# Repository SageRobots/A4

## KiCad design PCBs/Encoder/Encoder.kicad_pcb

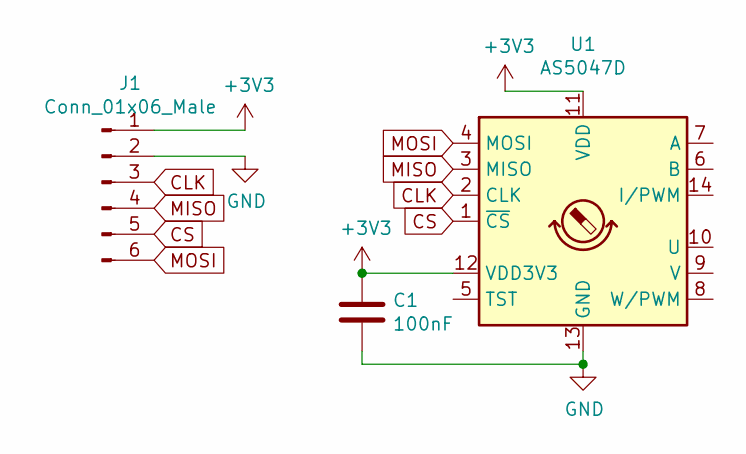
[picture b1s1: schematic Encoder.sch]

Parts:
C1: 100nF; C_0805_2012Metric_Pad1.18x1.45mm_HandSolder
J1: Conn_01x06_Male; PinHeader_2x03_P2.00mm_Vertical
U1: AS5047D; TSSOP-14_4.4x5mm_P0.65mm

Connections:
+3V3: C1.1, J1.1, U1.11 (VDD), U1.12 (VDD3V3)
CLK: J1.3, U1.2 (CLK)
CS: J1.5, U1.1 (~CS)
GND: C1.2, J1.2, U1.13 (GND)
MISO: J1.4, U1.3 (MISO)
MOSI: J1.6, U1.4 (MOSI)

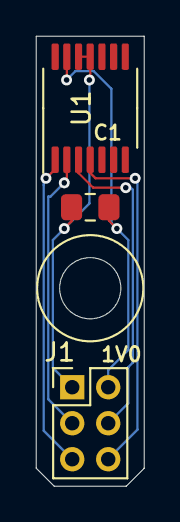
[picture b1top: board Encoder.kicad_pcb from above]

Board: 2 copper layers, 6.0 x 25.0 mm, 3 parts (0 on the bottom side), 6 nets.

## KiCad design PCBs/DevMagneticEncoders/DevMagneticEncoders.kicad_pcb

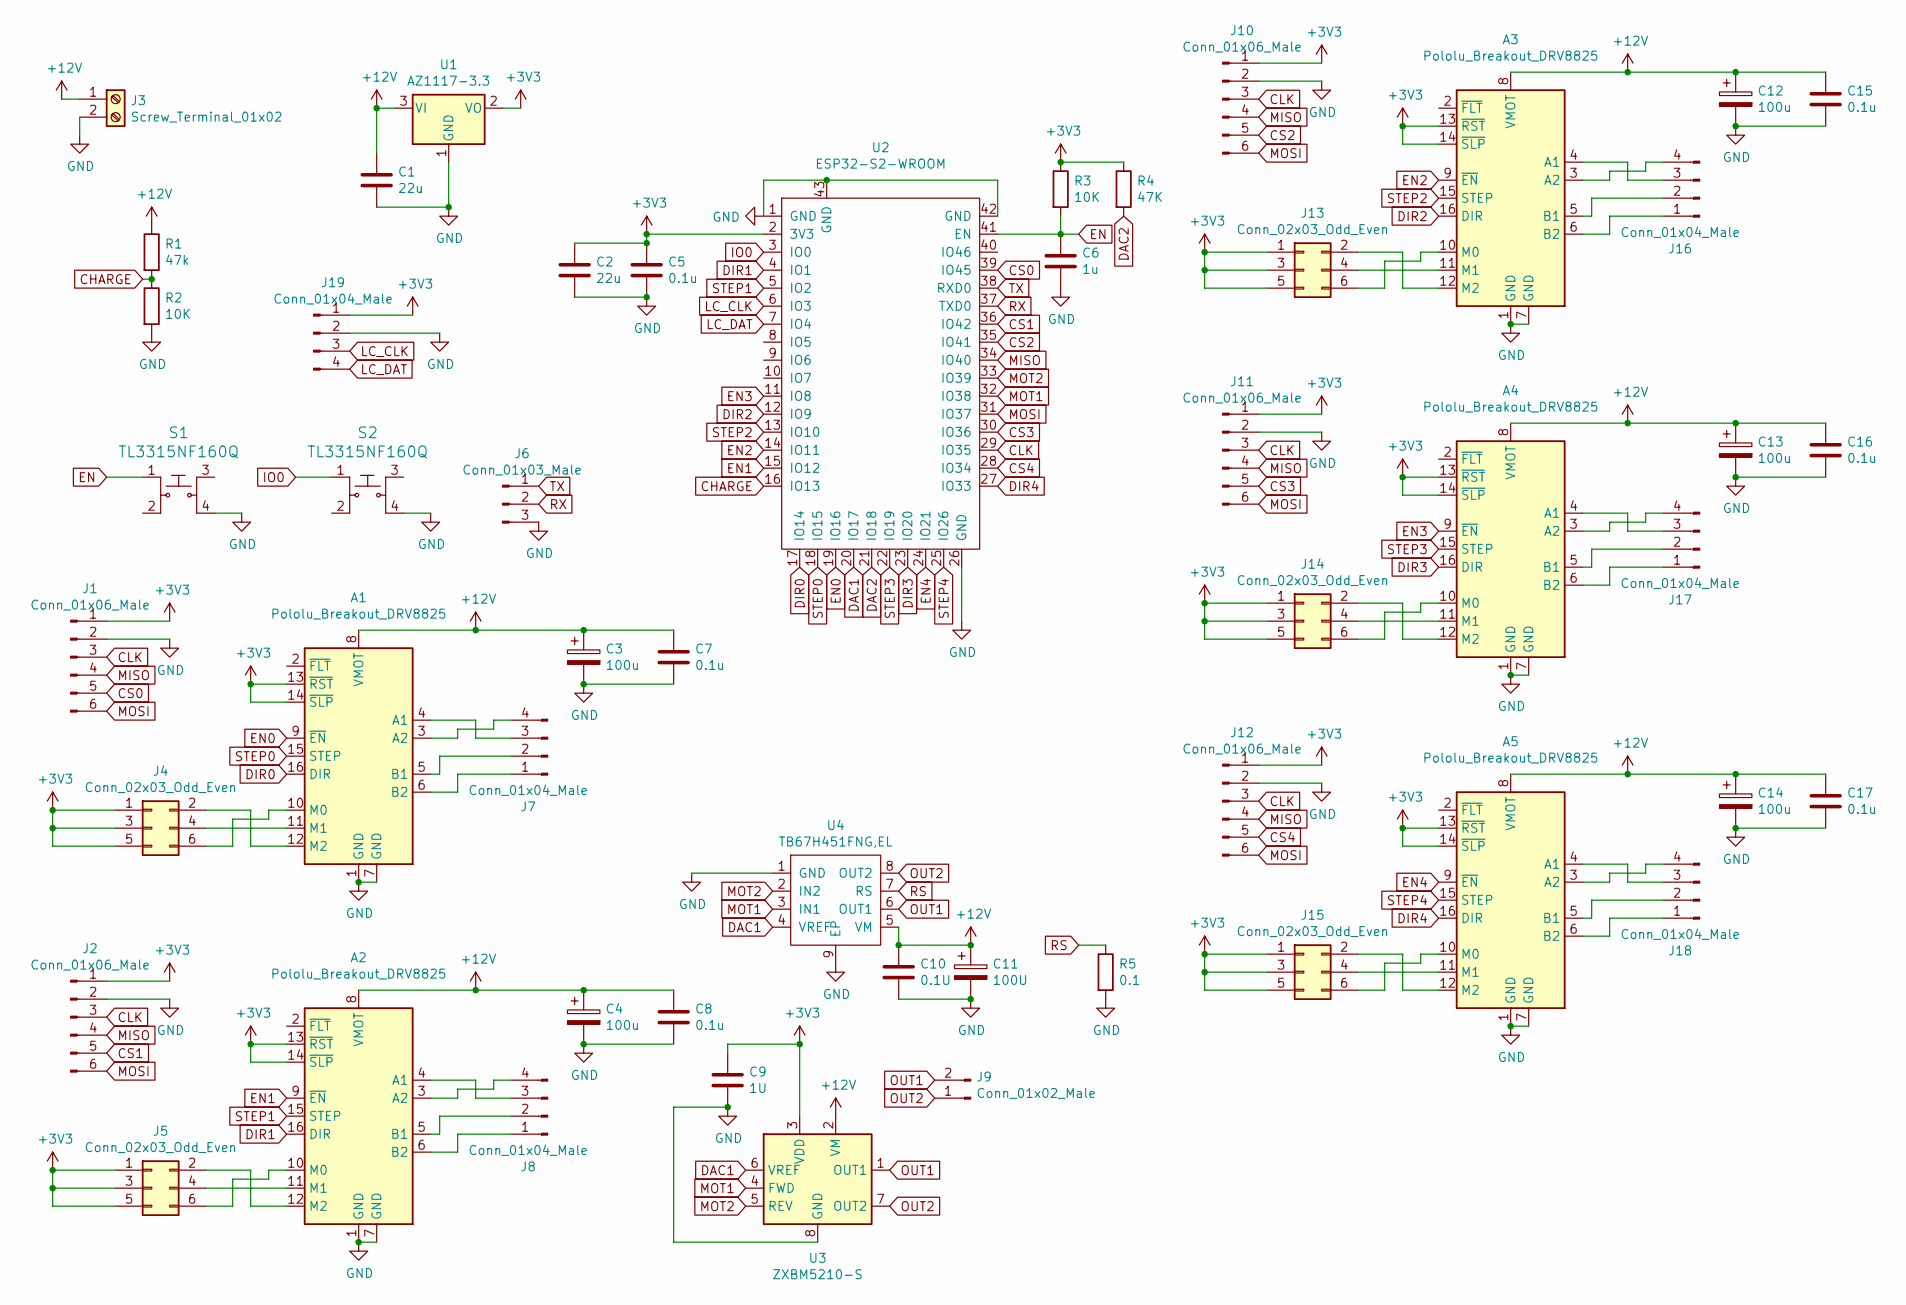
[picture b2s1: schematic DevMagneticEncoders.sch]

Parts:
A1, A2, A3, A4, A5: Pololu_Breakout_DRV8825; Pololu_Breakout-16_15.2x20.3mm
C1, C2: 22u; C_0805_2012Metric_Pad1.18x1.45mm_HandSolder
C3, C4, C12, C13, C14: 100u; CP_Elec_6.3x7.7
C5, C7, C8, C15, C16, C17: 0.1u; C_0805_2012Metric_Pad1.18x1.45mm_HandSolder
C6: 1u; C_0805_2012Metric_Pad1.18x1.45mm_HandSolder
C9: 1U; C_0805_2012Metric_Pad1.18x1.45mm_HandSolder
C10: 0.1U; C_0805_2012Metric_Pad1.18x1.45mm_HandSolder
C11: 100U; CP_Elec_6.3x7.7
J1, J2, J10, J11, J12: Conn_01x06_Male; JST_XH_B6B-XH-A_1x06_P2.50mm_Vertical
J3: Screw_Terminal_01x02; TerminalBlock_Phoenix_MKDS-1,5-2_1x02_P5.00mm_Horizontal
J4, J5, J13, J14, J15: Conn_02x03_Odd_Even; PinHeader_2x03_P2.54mm_Vertical
J6: Conn_01x03_Male; PinHeader_1x03_P2.54mm_Vertical
J7, J8, J16, J17, J18, J19: Conn_01x04_Male; JST_XH_B4B-XH-A_1x04_P2.50mm_Vertical
J9: Conn_01x02_Male; JST_XH_B2B-XH-A_1x02_P2.50mm_Vertical
R1: 47k; R_0805_2012Metric_Pad1.20x1.40mm_HandSolder
R2, R3: 10K; R_0805_2012Metric_Pad1.20x1.40mm_HandSolder
R4: 47K; R_0805_2012Metric_Pad1.20x1.40mm_HandSolder
R5: 0.1; R_0805_2012Metric_Pad1.20x1.40mm_HandSolder
S1, S2: TL3315NF160Q; TL3305AF160QG; MPN TL3315NF160Q; Digi-Key_PN EG4621CT-ND
U1: AZ1117-3.3; SOT-223-3_TabPin2
U2: ESP32-S2-WROOM
U3: ZXBM5210-S; SOIC-8_3.9x4.9mm_P1.27mm
U4: TB67H451FNG,EL; SOIC-8-1EP_3.9x4.9mm_P1.27mm_EP2.29x3mm_ThermalVias

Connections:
+3V3: A1.13 (~RST), A1.14 (~SLP), A2.13 (~RST), A2.14 (~SLP), A3.13 (~RST), A3.14 (~SLP), A4.13 (~RST), A4.14 (~SLP), A5.13 (~RST), A5.14 (~SLP), C2.1, C5.1, C9.1, J1.1, J2.1, J4.1, J4.3, J4.5, J5.1, J5.3, J5.5, J10.1, J11.1, J12.1, J13.1, J13.3, J13.5, J14.1, J14.3, J14.5, J15.1, J15.3, J15.5, J19.1, R3.1, R4.1, U1.2 (VO), U2.2 (3V3), U3.3 (VDD)
+12V: A1.8 (VMOT), A2.8 (VMOT), A3.8 (VMOT), A4.8 (VMOT), A5.8 (VMOT), C1.1, C3.1, C4.1, C7.1, C8.1, C10.1, C11.1, C12.1, C13.1, C14.1, C15.1, C16.1, C17.1, J3.1, R1.1, U1.3 (VI), U3.2 (VM), U4.5 (VM)
CHARGE: R1.2, R2.1, U2.16 (IO13)
CLK: J1.3, J2.3, J10.3, J11.3, J12.3, U2.29 (IO35)
CS0: J1.5, U2.39 (IO45)
CS1: J2.5, U2.36 (IO42)
CS2: J10.5, U2.35 (IO41)
CS3: J11.5, U2.30 (IO36)
CS4: J12.5, U2.28 (IO34)
DAC1: U2.20 (IO17), U3.6 (VREF), U4.4 (VREF)
DAC2: R4.2, U2.21 (IO18)
DIR0: A1.16 (DIR), U2.17 (IO14)
DIR1: A2.16 (DIR), U2.4 (IO1)
DIR2: A3.16 (DIR), U2.12 (IO9)
DIR3: A4.16 (DIR), U2.23 (IO20)
DIR4: A5.16 (DIR), U2.27 (IO33)
EN: C6.1, R3.2, S1.1, U2.41 (EN)
EN0: A1.9 (~EN), U2.19 (IO16)
EN1: A2.9 (~EN), U2.15 (IO12)
EN2: A3.9 (~EN), U2.14 (IO11)
EN3: A4.9 (~EN), U2.11 (IO8)
EN4: A5.9 (~EN), U2.24 (IO21)
GND: A1.1 (GND), A1.7 (GND), A2.1 (GND), A2.7 (GND), A3.1 (GND), A3.7 (GND), A4.1 (GND), A4.7 (GND), A5.1 (GND), A5.7 (GND), C1.2, C2.2, C3.2, C4.2, C5.2, C6.2, C7.2, C8.2, C9.2, C10.2, C11.2, C12.2, C13.2, C14.2, C15.2, C16.2, C17.2, J1.2, J2.2, J3.2, J6.3, J10.2, J11.2, J12.2, J19.2, R2.2, R5.2, S1.4, S2.4, U1.1 (GND), U2.1 (GND), U2.26 (GND), U2.42 (GND), U2.43 (GND), U3.8 (GND), U4.1 (GND), U4.9 (EP)
IO0: S2.1, U2.3 (IO0)
LC_CLK: J19.3, U2.6 (IO3)
LC_DAT: J19.4, U2.7 (IO4)
MISO: J1.4, J2.4, J10.4, J11.4, J12.4, U2.34 (IO40)
MOSI: J1.6, J2.6, J10.6, J11.6, J12.6, U2.31 (IO37)
MOT1: U2.32 (IO38), U3.4 (FWD), U4.3 (IN1)
MOT2: U2.33 (IO39), U3.5 (REV), U4.2 (IN2)
unnamed: A1.3 (A2), J7.4
unnamed: A1.4 (A1), J7.3
unnamed: A1.5 (B1), J7.2
unnamed: A1.6 (B2), J7.1
unnamed: A1.10 (M0), J4.6
unnamed: A1.11 (M1), J4.4
unnamed: A1.12 (M2), J4.2
unnamed: A2.3 (A2), J8.4
unnamed: A2.4 (A1), J8.3
unnamed: A2.5 (B1), J8.2
unnamed: A2.6 (B2), J8.1
unnamed: A2.10 (M0), J5.6
unnamed: A2.11 (M1), J5.4
unnamed: A2.12 (M2), J5.2
unnamed: A3.3 (A2), J16.4
unnamed: A3.4 (A1), J16.3
unnamed: A3.5 (B1), J16.2
unnamed: A3.6 (B2), J16.1
unnamed: A3.10 (M0), J13.6
unnamed: A3.11 (M1), J13.4
unnamed: A3.12 (M2), J13.2
unnamed: A4.3 (A2), J17.4
unnamed: A4.4 (A1), J17.3
unnamed: A4.5 (B1), J17.2
unnamed: A4.6 (B2), J17.1
unnamed: A4.10 (M0), J14.6
unnamed: A4.11 (M1), J14.4
unnamed: A4.12 (M2), J14.2
unnamed: A5.3 (A2), J18.4
unnamed: A5.4 (A1), J18.3
unnamed: A5.5 (B1), J18.2
unnamed: A5.6 (B2), J18.1
unnamed: A5.10 (M0), J15.6
unnamed: A5.11 (M1), J15.4
unnamed: A5.12 (M2), J15.2
OUT1: J9.2, U3.1 (OUT1), U4.6 (OUT1)
OUT2: J9.1, U3.7 (OUT2), U4.8 (OUT2)
RS: R5.1, U4.7 (RS)
RX: J6.2, U2.37 (TXD0)
STEP0: A1.15 (STEP), U2.18 (IO15)
STEP1: A2.15 (STEP), U2.5 (IO2)
STEP2: A3.15 (STEP), U2.13 (IO10)
STEP3: A4.15 (STEP), U2.22 (IO19)
STEP4: A5.15 (STEP), U2.25 (IO26)
TX: J6.1, U2.38 (RXD0)

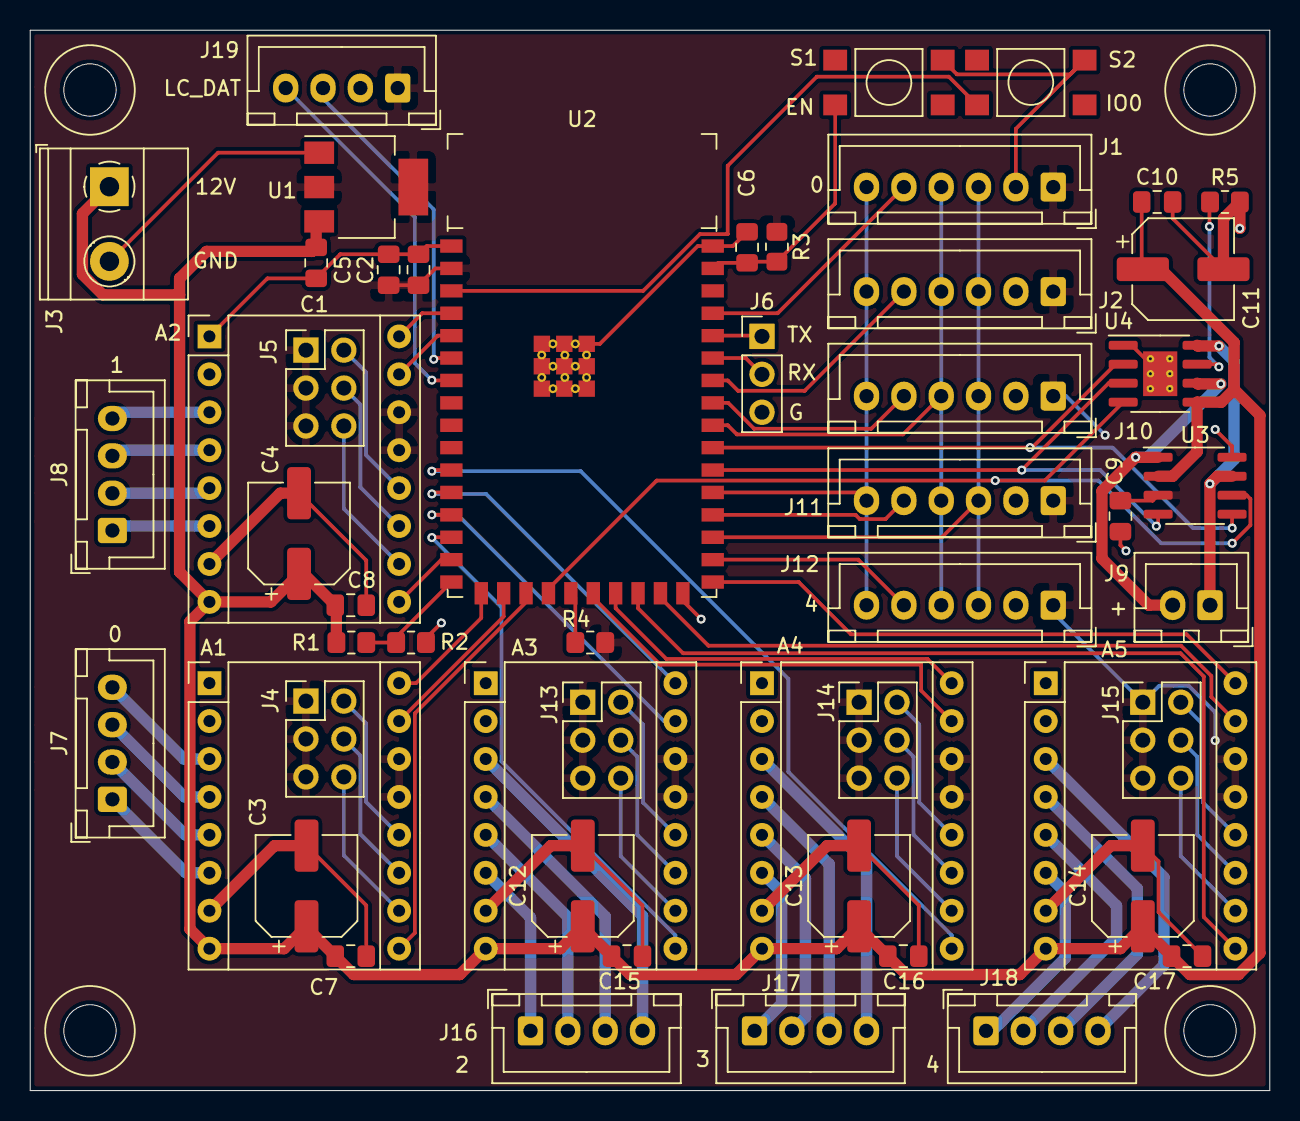
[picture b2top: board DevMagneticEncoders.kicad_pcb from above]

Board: 2 copper layers, 83.0 x 71.0 mm, 52 parts (0 on the bottom side), 75 nets.

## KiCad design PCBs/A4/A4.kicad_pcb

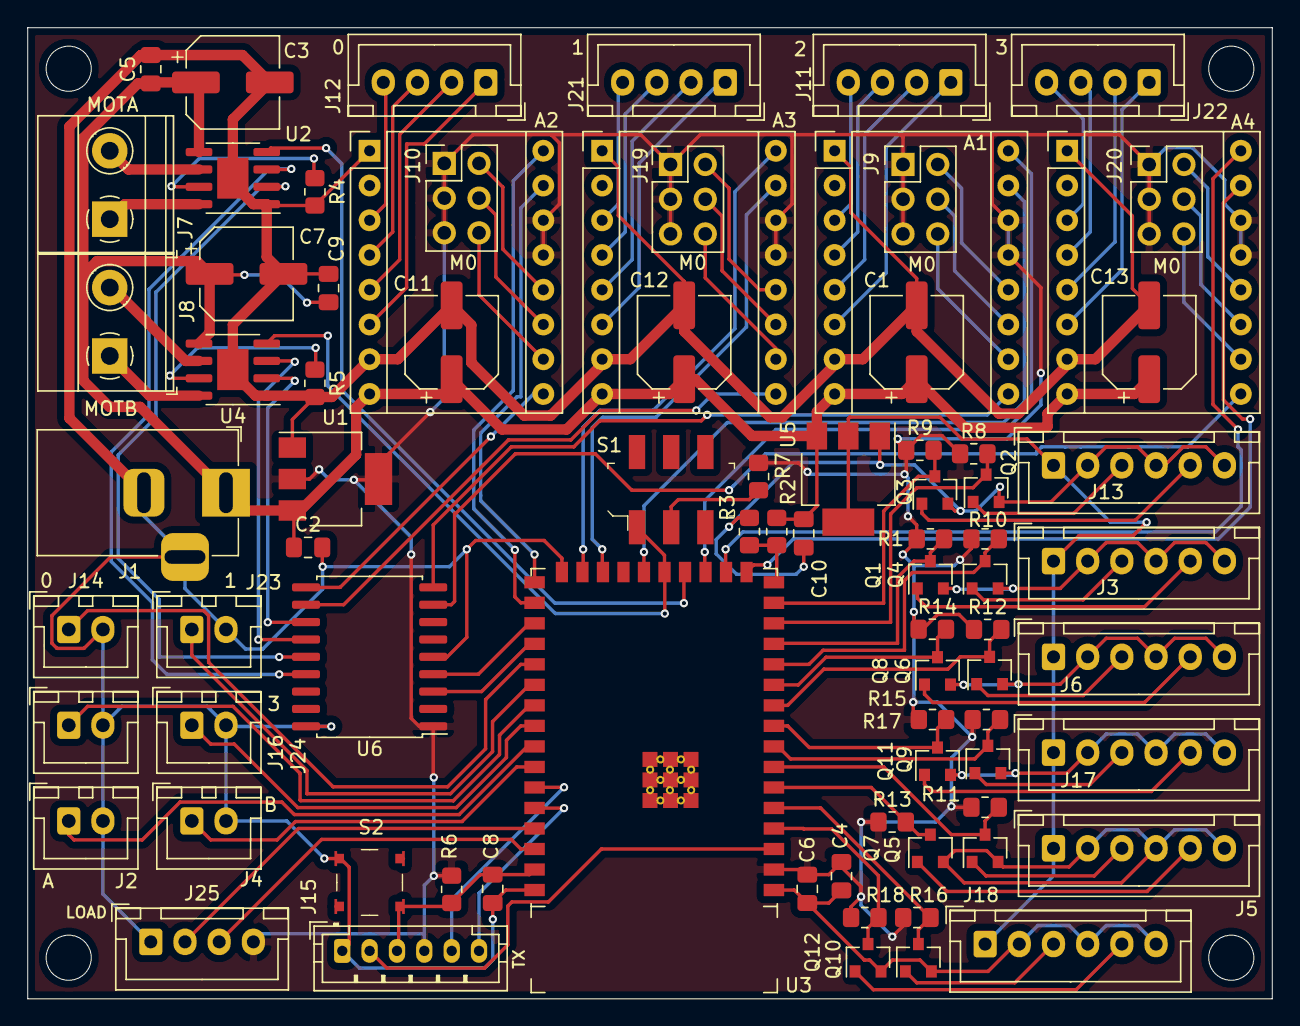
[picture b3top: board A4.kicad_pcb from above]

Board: 2 copper layers, 91.0 x 71.0 mm, 80 parts (0 on the bottom side), 96 nets.

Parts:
A1, A2, A3, A4: Pololu_Breakout_DRV8825; Pololu_Breakout-16_15.2x20.3mm
C1, C3, C7, C11, C12, C13: 100u; CP_Elec_6.3x7.7
C2, C4, C10: 22u; C_0805_2012Metric_Pad1.18x1.45mm_HandSolder
C5, C6, C9: 0.1u; C_0805_2012Metric_Pad1.18x1.45mm_HandSolder
C8: 1u; C_0805_2012Metric_Pad1.18x1.45mm_HandSolder
J1: Barrel_Jack_Switch; BarrelJack_Horizontal
J2, J4, J14, J16, J23, J24: Conn_01x02_Male; JST_XH_B2B-XH-A_1x02_P2.50mm_Vertical
J3, J5, J6, J13, J17, J18: Conn_01x06_Male; JST_XH_B6B-XH-A_1x06_P2.50mm_Vertical
J7, J8: Screw_Terminal_01x02; TerminalBlock_Phoenix_MKDS-1,5-2_1x02_P5.00mm_Horizontal
J9, J10, J19, J20: Conn_02x03_Odd_Even; PinHeader_2x03_P2.54mm_Vertical
J11, J12, J21, J22, J25: Conn_01x04_Male; JST_XH_B4B-XH-A_1x04_P2.50mm_Vertical
J15: Conn_01x06_Male; JST_PH_B6B-PH-K_1x06_P2.00mm_Vertical
Q1, Q2, Q3, Q4, Q5, Q6, Q7, Q8, Q9, Q10, Q11, Q12: 2N7002; SOT-23
R1, R3, R6, R8, R9, R10, R11, R12, R13, R14, R15, R16, R17, R18: 10K; R_0805_2012Metric_Pad1.20x1.40mm_HandSolder
R2: 47k; R_0805_2012Metric_Pad1.20x1.40mm_HandSolder
R4, R5: 0.1; R_0805_2012Metric_Pad1.20x1.40mm_HandSolder
R7: 47K; R_0805_2012Metric_Pad1.20x1.40mm_HandSolder
S1: JS202011SCQN; Switch_Slide_JS202011SCQN
S2: TL3315NF160Q; Switch_Tactile_SMD_4.5x4.5mm_TL3315NF160Q
U1: AZ1117-3.3; SOT-223-3_TabPin2
U2, U4: TB67H451FNG,EL; SOIC-8-1EP_3.9x4.9mm_P1.27mm_EP2.29x3mm
U3: ESP32-S2-WROOM
U5: AZ1117-5.0; SOT-223-3_TabPin2
U6: MCP23009; SOIC-18W_7.5x11.6mm_P1.27mm

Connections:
+3V3: A1.13, A1.14, A2.13, A2.14, A3.13, A3.14, A4.13, A4.14, C4.1, C6.1, J9.1, J9.3, J9.5, J10.1, J10.3, J10.5, J15.4, J19.1, J19.3, J19.5, J20.1, J20.3, J20.5, J25.4, R1.1, R6.1, R7.1, R8.1, R9.1, R10.1, R11.1, R12.1, R13.1, R14.1, R15.1, R16.1, R17.1, R18.1, U1.2, U3.2, U6.1
+5V: J3.1, J5.1, J6.1, J13.1, J17.1, J18.1, U5.2
+12V: A1.8, A2.8, A3.8, A4.8, C1.1, C2.1, C3.1, C5.1, C7.1, C9.1, C10.1, C11.1, C12.1, C13.1, J1.1, R2.1, U1.3, U2.5, U4.5, U5.3
CHARGE: R2.2, R3.1, U3.16
CLK: J25.3, U3.40
DAC1: U2.4, U3.20
DAC2: S1.1, U3.21, U4.4
DAT: J25.2, U3.39
DIR0: A2.16, U3.28
DIR1: A3.16, U3.25
DIR2: A1.16, U3.19
DIR3: A4.16, U3.18
EN: C8.1, J15.3, R6.2, S2.1, U3.41
EN0: A2.9, U6.10
EN1: A3.9, U6.11
EN2: A1.9, U6.9
EN3: A4.9, U6.8
ENC0A: Q6.3, R12.2, U3.10
ENC0A_5V: J6.3, Q6.1
ENC0B: Q8.3, R14.2, U3.11
ENC0B_5V: J6.5, Q8.1
ENC1A: Q9.3, R15.2, U3.8
ENC1A_5V: J17.3, Q9.1
ENC1B: Q11.3, R17.2, U3.9
ENC1B_5V: J17.5, Q11.1
ENC2A: Q5.3, R11.2, U3.7
ENC2A_5V: J5.3, Q5.1
ENC2B: Q7.3, R13.2, U3.6
ENC2B_5V: J5.5, Q7.1
ENC3A: Q10.3, R16.2, U3.5
ENC3A_5V: J18.3, Q10.1
ENC3B: Q12.3, R18.2, U3.4
ENC3B_5V: J18.5, Q12.1
ENCAA: Q2.3, R8.2, U3.14
ENCAA_5V: J13.3, Q2.1
ENCAB: Q3.3, R9.2, U3.15
ENCAB_5V: J13.5, Q3.1
ENCBA: Q4.3, R10.2, U3.12
ENCBA_5V: J3.3, Q4.1
ENCBB: Q1.3, R1.2, U3.13
ENCBB_5V: J3.5, Q1.1
GND: A1.1, A1.7, A2.1, A2.7, A3.1, A3.7, A4.1, A4.7, C1.2, C2.2, C3.2, C4.2, C5.2, C6.2, C7.2, C8.2, C9.2, C10.2, C11.2, C12.2, C13.2, J1.2, J1.3, J2.2, J3.2, J3.4, J3.6, J4.2, J5.2, J5.4, J5.6, J6.2, J6.4, J6.6, J13.2, J13.4, J13.6, J14.2, J15.1, J16.2, J17.2, J17.4, J17.6, J18.2, J18.4, J18.6, J23.2, J24.2, J25.1, Q1.2, Q2.2, Q3.2, Q4.2, Q5.2, Q6.2, Q7.2, Q8.2, Q9.2, Q10.2, Q11.2, Q12.2, R3.2, R4.2, R5.2, S2.4, U1.1, U2.1, U2.9, U3.1, U3.26, U3.42, U4.1, U4.9, U5.1, U6.5, U6.18
HOM0: J14.1, U3.31
HOM1: J23.1, U3.32
HOM2: J16.1, U3.33
HOM3: J24.1, U3.34
HOMA: J2.1, U3.35
HOMB: J4.1, U3.36
IO0: J15.2, U3.3
MOTA1: U2.3, U6.15
MOTA2: U2.2, U6.14
MOTB1: U4.3, U6.13
MOTB2: U4.2, U6.12
unnamed: A1.3, J11.4
unnamed: A1.4, J11.3
unnamed: A1.5, J11.2
unnamed: A1.6, J11.1
unnamed: A1.10, J9.6
unnamed: A1.11, J9.4
unnamed: A1.12, J9.2
unnamed: A2.3, J12.4
unnamed: A2.4, J12.3
unnamed: A2.5, J12.2
unnamed: A2.6, J12.1
unnamed: A2.10, J10.6
unnamed: A2.11, J10.4
unnamed: A2.12, J10.2
unnamed: A3.3, J21.4
unnamed: A3.4, J21.3
unnamed: A3.5, J21.2
unnamed: A3.6, J21.1
unnamed: A3.10, J19.6
unnamed: A3.11, J19.4
unnamed: A3.12, J19.2
unnamed: A4.3, J22.4
unnamed: A4.4, J22.3
unnamed: A4.5, J22.2
unnamed: A4.6, J22.1
unnamed: A4.10, J20.6
unnamed: A4.11, J20.4
unnamed: A4.12, J20.2
unnamed: J7.1, U2.8
unnamed: J7.2, U2.6
unnamed: J8.1, U4.8
unnamed: J8.2, U4.6
unnamed: R7.2, S1.2
RSA: R4.1, U2.7
RSB: R5.1, U4.7
RX: J15.5, U3.37
SCL: U3.30, U6.3
SDA: U3.29, U6.4
STEP0: A2.15, U3.27
STEP1: A3.15, U3.24
STEP2: A1.15, U3.22
STEP3: A4.15, U3.17
TX: J15.6, U3.38

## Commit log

2021-02-20 added files
2021-02-22 gripper
2021-02-22 STLs
2021-02-22 added belt
2021-02-23 groups
2021-02-23 ungroup
2021-02-23 added thrust 40 60
2021-02-24 lengthen humerus
2021-02-24 manual
2021-02-27 base
2021-02-28 base j2 update
2021-02-28 home switches
2021-03-01 site
2021-03-02 rename limit switch LCS
2021-03-04 j1 base update
2021-03-04 stl renaming
2021-03-05 tensioner using flat head
2021-03-09 Revert "stl renaming"
    This reverts commit 35aa1277a2ccd7e2b800057be5858a70b133cdcb.
2021-03-09 Revert "Revert "stl renaming""
    This reverts commit f7a140d2211aad14199da15265b41ba0777b9a48.
2021-03-09 Revert "meh"
    This reverts commit ab2f53892d5ed5ff219349ce895dddebeb2109ec.
2021-03-09 Revert "tensioner using flat head"
    This reverts commit 17175318791108bdd8a99ea1b029147a4a21936e.
2021-03-09 reverted some changes and redid
    versions may have messed up some files
2021-03-10 freeCAD 24267
2021-03-11 cable routing updates
2021-03-12 slots in gripper motor bracket STL
2021-03-12 added code
2021-03-12 updated pins in code
2021-03-13 stepper class
2021-03-13 compiles
2021-03-13 com class
2021-03-13 joint 0 functional
2021-03-15 more clearance for fingertip
2021-03-16 completely tested
2021-03-16 added gripper class
2021-03-22 renamed stls
2021-04-06 update stl name
2021-04-06 stl names updated
2021-04-29 PCB ready to order
2021-04-30 gerber files
2021-05-17 PCB order
2021-05-17 magnetic encoder j0
2021-05-17 j1 base
2021-05-17 J0 stls
2021-05-18 dev board
2021-05-19 ordered boards
2021-05-28 gcode
2021-06-29 working spi encoder com
2021-07-31 2.0 cad updates
2021-08-03 J1 design complete
2021-08-08 J0 and J1 encoders
2021-08-09 5 stepper board
2021-08-09 ready to order
2021-08-10 added load cell connector
2021-08-20 J2 IP
2021-08-21 finished J2
2021-09-14 heat set hole size update
2021-09-24 separate gripper
2021-09-25 added gripper
2021-09-29 paint roller
2021-10-15 riser hole template
2021-10-15 J0-ENCODER-BRACKET
2021-10-16 pcb bracket
2021-10-16 Remove GCode folder
2021-10-18 2 motors moving
2021-10-20 encoder PCB update
    datum relief and traces on bottom
2021-11-04 J0_ENCODER_BRACKET Update
    Using screws for plastic instead of heat-set inserts
2021-11-06 J0_ENCODER_BRACKET update
    More clearance for connector
2021-11-06 J0 code
2021-11-08 J1 updates
    Using screws for plastic
2021-11-09 Master accel debugged
2021-11-10 J0 and J1 functional
2021-11-25 J1, J2, J3 functional
    Need to set offsets and add J4
2021-11-27 J3 updates
2021-12-01 Update A4.c
    untested, update speed with separate 5ms timer
2021-12-01 Update A4.c
    J0 speed from displacement functional
2021-12-01 Update A4.c
    all axes functional
    J3 needs lower speedMax
    joint home offsets needed
2021-12-02 Update A4.c
    offsets applied
2021-12-03 J1 and J2 updates
    J1 switched to metric coupler
    J2 improved belt tensioning
2021-12-03 Update A4.c
    J3 speed max set
2021-12-06 Update A4.c
    Switching to position error control
2021-12-11 Update A4.c
    started multi axis time master moves
2021-12-16 Update A4.c
    untested multi-axis p control
2021-12-17 Update A4.c
    tested single axis moves
2021-12-28 Added paint roller to model
2021-12-30 forward kinematics complete
2022-01-02 inverse kinematics functional
2022-01-03 working paint script
2022-01-04 video script
2022-01-06 started bldc design
2022-02-12 added BOM, removed obsolete PCB
2022-03-02 Encoder silkscreen update
